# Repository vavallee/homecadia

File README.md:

<h1 align="center">
  <picture>
    <source media="(prefers-color-scheme: dark)" srcset="docs/img/logo-dark.svg">
    
  </picture>
</h1>

<!-- Logo: the Grand-Pré Memorial Church (Grand-Pré National Historic Site, Nova
     Scotia) behind the case wordmark; drawn without religious symbols. -->

**A battery-powered Matter-over-Thread room sensor for Home Assistant, built
from scratch on the ESP32-C6 with esp-matter and ESP-IDF. 125 µA average,
e-ink display, rotary dial, no cloud, no Wi-Fi, and every trap written down.**

<!-- photo replaces the render once a unit is assembled:  -->

A room temperature and humidity sensor that reports to Home Assistant over
Thread as a Matter sleepy end device, shows its own readings on a 2.9" e-ink
panel, and takes input from a rotary dial. It averages **125 µA** measured on
the bench, about eighteen months on one 2000 mAh cell at 85 % usable. No vendor
cloud, no hub beyond a Thread border router, and no Wi-Fi: the radio is
compiled out.

Everything is here: firmware, drivers, pin map with schematic-verified board
facts, measured power budget, 3D-printable enclosure, bill of materials with
real prices, and the reasoning behind each decision, including the ones that
turned out wrong.

## At a glance

| | |
|---|---|
| MCU | Seeed XIAO ESP32-C6 (RISC-V, 802.15.4 + BLE; Wi-Fi compiled out) |
| Firmware | **aardvark** (Matter model name and version string, e.g. `aardvark 0.7.0`; build output `aardvark.bin`, OTA image `aardvark-<version>.ota`) |
| Stack | [esp-matter](https://github.com/espressif/esp-matter) v1.6 on ESP-IDF v5.5.5, C++ |
| Network | Matter over Thread, OpenThread minimal device (MTD), commissioned over BLE |
| Power mode | Intermittently Connected Device (ICD), short idle time: 15 s parent polls, 600 s idle interval, automatic light sleep |
| Controller | Home Assistant with matterjs-server, Home Assistant Connect ZBT-2 border router |
| Clusters | Temperature Measurement, Relative Humidity Measurement, Power Source (battery % and voltage), Thread Network Diagnostics with counters |
| Measured current | **125 µA** paired and settled (sleep floor 57 µA, parent poll ~0.48 mC); **19.7 µA** unpaired in deep sleep |
| Display | 2.9" 296×128 SSD1680 e-paper, partial refresh ~6–7.5 mC, full ~19 mC |
| Status | One unit bench-verified on a Nordic PPK2; enclosure being redesigned |

## If you are building Matter or Thread devices on an ESP32

Most of this repo is reusable even if you never build this sensor. The
findings that took longest, with where to read them:

| Topic | Where |
|---|---|
| Getting an ESP32-C6 Matter device from ~376 µA to 125 µA: ADC power domain, bus power-down flags, ICD mode, a pin regression | [power-budget.md](docs/power-budget.md), [field-notes](docs/field-notes.md) §20–§22, §28 |
| Long Idle Time ICD buys nothing with Home Assistant (no check-in client) and costs ~67 µA; what to use instead | [retro](docs/retro.md) M8, [sdkconfig.defaults](firmware/sensor-01/sdkconfig.defaults) |
| A non-wake GPIO with a level interrupt under `CONFIG_PM_SLP_DISABLE_GPIO`: +16 µA floor, polls 60 % dearer | [field-notes](docs/field-notes.md) §28 |
| Waking light sleep from a rotary encoder: LP GPIOs only, level not edge | [field-notes](docs/field-notes.md) §21, [`ec11_encoder`](firmware/components/ec11_encoder) |
| An unpaired Matter device draws 28 mA; deep sleep that works (restart, then sleep before the stack starts) | [field-notes](docs/field-notes.md) §26–§27 |
| `attribute::update()` silently does nothing for code-driven clusters in esp-matter v1.6 | [field-notes](docs/field-notes.md) §9 |
| Commissioning to Home Assistant without HAOS: test certificates, BLE proxy, border router | [commissioning.md](docs/commissioning.md) |
| Thread coverage, border-router outages, a bare XIAO ESP32-C6 as a Thread router | [field-notes](docs/field-notes.md) §6–§7, §24, [infrastructure.md](docs/infrastructure.md), [bringup.md](docs/bringup.md) Radio / Matter |
| Measuring µA on a sleepy radio device with a PPK2, and analysing captures offline | [`tools/ppk2-events.py`](tools/ppk2-events.py), [retro](docs/retro.md) T7–T9 |
| Hardware bring-up traps: FPC ribbons, flux, underside pads, breadboard battery paths | [assembly.md](docs/assembly.md), [battery-runbook.md](docs/battery-runbook.md), [field-notes](docs/field-notes.md) §15–§19, §25 |
| Eight weeks of bring-up in one place: what went wrong, why, and the checklist for the next unit | [retro.md](docs/retro.md) |

> **Status: bench-verified, not yet assembled.** One unit runs on the bench
> (XIAO, driver board, panel, SHT40, encoder on a breadboard) with a Nordic
> PPK2 standing in for the cell. Verified there: commissioning to Home
> Assistant over Thread, display output, battery-voltage reading (within 3 mV
> of a meter, 3.4–4.0 V), **125 µA settled paired current** (2026-10-05),
> 19.7 µA unpaired deep sleep, and the dial waking the chip from light sleep on
> battery power. It has run 21 h on a real LiPo with no restart. **Not yet
> done:** a long soak on a real cell, and the enclosure, which is being
> redesigned. Open rows are in [docs/bringup.md](docs/bringup.md); code written
> ahead of hardware is marked `HW-VERIFY` and tracked there. The build
> procedure, with a test gate after every soldering stage, is
> [docs/assembly.md](docs/assembly.md).

## Devices

| Device | Status | Description |
|---|---|---|
| [sensor-01](firmware/sensor-01/) | in development | Battery-powered room temp/humidity sensor. 2.9" e-ink display, rotary dial, Matter-over-Thread sleepy end device (SIT ICD). 3 units. |

## What you can lift from here

The drivers are self-contained ESP-IDF components with no dependencies beyond
the IDF itself. Copy the directory into your own `components/` and it builds.
MIT licensed.

| Component | Why it might be useful |
|---|---|
| [`sht40`](firmware/components/sht40) | Sensirion SHT40 on the ESP-IDF 5.x `i2c_master` API (not the deprecated legacy driver), high-precision single-shot with CRC-8 validation |
| [`ssd1680`](firmware/components/ssd1680) | 2.9" e-paper with **differential partial refresh**, periodic full refresh to clear ghosting, and panel deep sleep between updates — the parts most sample code leaves out |
| [`monogfx`](firmware/components/monogfx) | 1-bit framebuffer renderer with a scaled 5×7 font and a seven-segment digit routine. No LVGL, no external graphics library |
| [`ec11_encoder`](firmware/components/ec11_encoder) | EC11 rotary encoder decoded from a Gray-code transition table in an ISR — bounce-immune without debounce delays, and draws no idle current |

Tools, usable on any project:

| Tool | What it does |
|---|---|
| [`tools/ppk2-events.py`](tools/ppk2-events.py) | Reads a Nordic PPK2 `.ppk2` capture offline and splits it into sleep floor, radio polls, bursts and short wakes with their charge, so one capture gives a per-item current budget |
| [`tools/matter-node.py`](tools/matter-node.py) | Reads a node through the Home Assistant Matter server WebSocket: the cached attributes (free for the device) or a forced interview |
| [`tools/check-profiles.sh`](tools/check-profiles.sh) | Asserts a shipping and a bench sdkconfig really differ on sleep, and that test-only options are off in shipping. Runs in CI |

Also reusable regardless of hardware: the
[power budget](docs/power-budget.md) and the firmware policies it forced, the
[retro](docs/retro.md), and the [documented traps](#traps-that-cost-time)
below.

## Features

Firmware capabilities, all implemented in this repo unless noted:

- **Matter over Thread**, Wi-Fi compiled out. OpenThread MTD, commissioned over
  Bluetooth Low Energy, joins via any OpenThread border router (developed
  against Home Assistant Connect ZBT-2).
- **Short Idle Time ICD** (Intermittently Connected Device): automatic light
  sleep between 15 s parent polls, and a 600 s idle interval that the device
  offers as its subscription max interval, so a report with nothing new goes
  out every 10 min. Long Idle Time was dropped on 2026-10-04: Home Assistant
  registers no check-in client, so it only added cost
  ([retro](docs/retro.md) M8).
- **Unpaired deep sleep**: a unit nobody pairs deep-sleeps at 19.7 µA once
  its 15-minute commissioning window closes, and a turn of the dial starts a
  new window ([field-notes](docs/field-notes.md) §27).
- **Thread Network Diagnostics with counters** (attach attempts, parent
  changes, MAC retries), readable from the controller at no reporting cost.
- **Matter clusters**: TemperatureMeasurement, RelativeHumidityMeasurement, and
  PowerSource with battery percentage and voltage.
- **Delta-gated reporting** — a report is sent on ≥0.2 °C / ≥1 %RH change, with
  a forced heartbeat every N polls, instead of on every sample.
- **SHT40 driver** (`firmware/components/sht40`) on the ESP-IDF 5.x
  `i2c_master` API, high-precision single-shot with Sensirion CRC-8 checking.
- **SSD1680 e-paper driver** (`firmware/components/ssd1680`) with differential
  partial refresh, periodic full refresh for ghosting, and panel deep sleep
  between updates.
- **1-bit framebuffer renderer** (`firmware/components/monogfx`) with a scaled
  5×7 font and a seven-segment digit routine — no external graphics library.
- **EC11 rotary encoder** (`firmware/components/ec11_encoder`) decoded from a
  Gray-code transition table in an interrupt handler: bounce-immune and drawing
  no idle current.
- **Local-only UI**: readings, diagnostics, and settings views; settings persist
  in NVS. The display never renders Home Assistant state — it shows what this
  device measured.
- **Battery monitoring** via a 2×1 MΩ + 100 nF divider on GPIO4 (an underside
  pad): 64 one-shot ADC samples after a 20 ms settle, eFuse curve-fitting
  calibration, and a scale factor fitted against a metered source to correct the
  ADC input loading the 500 kΩ divider. Open-circuit-voltage lookup table for
  percent.
- **Dial wakes the chip** from light sleep on a detent (encoder A on an LP
  GPIO underside pad, level-triggered).
- **Factory reset** on a 10-second encoder press (turn first: the switch is on
  a pin that cannot wake the chip); commissioning and low-battery states shown
  on a single LED and on the display.
- **CI** builds the flashable images on every push touching `firmware/**` and
  uploads them as an artifact.

## sensor-01 hardware

Seeed XIAO ESP32-C6 + Seeed ePaper Driver Board for XIAO V2 + 2.9" mono e-ink
(296×128, SSD1680) + Grove SHT40 + EC11 rotary encoder + 2000mAh LiPo, in a
wall-mount enclosure remixed from [veltoc](https://github.com/danking6/veltoc)
([hardware/case](hardware/case/README.md) — rev 4, FDM PLA, laser-engraved
wordmark).

*Assembled view rendered from the enclosure STLs. Colours and finish are
indicative; no unit has been built yet.*

Full bill of materials: [docs/bom.md](docs/bom.md). Pin map with the
schematic-verified board facts behind this diagram:
[docs/pinmap.md](docs/pinmap.md). The official bare-board pinout is on the
[Seeed XIAO ESP32-C6 wiki](https://wiki.seeedstudio.com/xiao_esp32c6_getting_started/)
(not reproduced here — Seeed's wiki content is GPL-3.0, this repo is MIT).

⚠️ This build involves a bare lithium-polymer cell soldered directly to the
board. Read the polarity warning at the top of
[docs/assembly.md](docs/assembly.md) before connecting anything — reversed
polarity destroys the charge circuit, and damaged LiPo cells are a fire hazard.

## Firmware

Espressif [esp-matter](https://github.com/espressif/esp-matter) v1.6 on
ESP-IDF v5.5.5, C++. Thread only (Wi-Fi disabled), commissions over Bluetooth
Low Energy to Home Assistant via an OpenThread border router (Home Assistant
Connect ZBT-2). Build instructions: [docs/build.md](docs/build.md).

The device advertises Espressif's **test vendor ID 0xFFF1** and shared test
commissioning credentials. It is not a Matter-certified product; controllers
will show an uncertified-device warning. Per-device factory partitions
(`esp-matter-mfg-tool`) are an open work item — see
[docs/commissioning.md](docs/commissioning.md).

## Documentation

| Doc | Contents |
|---|---|
| [docs/bom.md](docs/bom.md) | Bill of materials, part SKUs, divider-value rationale |
| [docs/pinmap.md](docs/pinmap.md) | Pin assignments and schematic-verified XIAO ESP32-C6 board facts |
| [docs/assembly.md](docs/assembly.md) | Wiring and build order, battery-polarity warning |
| [docs/build.md](docs/build.md) | Pinned toolchain SHAs, Docker and native builds, flashing from WSL2 |
| [docs/commissioning.md](docs/commissioning.md) | Pairing to Home Assistant: the three preconditions, the BLE-proxy workaround, factory reset. Apple Home is not available here and the doc says why |
| [docs/retro.md](docs/retro.md) | **Retrospective of the whole bring-up**: lessons, timeline, every problem with its cause and rule, the checklist for the next unit, open questions |
| [docs/field-notes.md](docs/field-notes.md) | **Traps that cost real time during bring-up**, one numbered section per incident (cited as §n). Read before bringing up another unit |
| [docs/power-budget.md](docs/power-budget.md) | Modelled and measured current draw per item, battery-life calculator, the policies it forced |
| [docs/battery-runbook.md](docs/battery-runbook.md) | Why a pack reads 0 V or a unit resets on battery: protection-board causes, look-alikes, and the test order |
| [docs/bringup.md](docs/bringup.md) | Hardware verification checklist — every `HW-VERIFY` marker has a row |
| [docs/diagrams/](docs/diagrams/) | Bench wiring, battery/divider schematic, enclosure internals and the no-solder bring-up ladder (self-contained HTML) |
| [docs/infrastructure.md](docs/infrastructure.md) | Network-side hardware: ZBT-2 border router, Thread coverage, Voice PE, order status |
| [docs/source-reliability.md](docs/source-reliability.md) | Documented traps in vendor docs and third-party sources |
| [hardware/case/README.md](hardware/case/README.md) | Enclosure: revision history, measured wall thicknesses, print vendor and material, engraving artwork |
| [circuit-board-maker/](circuit-board-maker/README.md) | Custom-PCB evaluation and two paper board designs. **Concluded: not worth it for three units.** Never fabricated — see the conflicts list before reviving it |

## Traps that cost time

Findings that aren't in any datasheet, written down so the next person doesn't
pay for them twice. Full list in
[docs/source-reliability.md](docs/source-reliability.md) and
[docs/pinmap.md](docs/pinmap.md).

- **A0 and D0 are the same pin on the XIAO ESP32-C6.** If your display uses D0
  for reset, the obvious ADC pin is gone. Battery sense moved to an underside
  test pad ([pinmap](docs/pinmap.md)).
- **The C6's RF switch is off at reset.** GPIO3 has a 10k pull-up and must be
  driven low in firmware before the antenna works; GPIO14 selects onboard
  ceramic versus U.FL. Neither pin is on the header. Schematic-verified.
- **espboards.dev pin tables are wrong for the C6** — they're shared boilerplate
  across ESP32 variants.
- **The Seeed wiki's battery-sense snippet doesn't apply.** It assumes an
  onboard divider the C6 schematic shows isn't populated.
- **A 100k battery divider costs ~9% of a 300µA budget.** 2×1MΩ + 100nF instead,
  at the price of a high-impedance ADC source ([power budget](docs/power-budget.md)).
- **A live ADC unit keeps the C6's radio power domain on through every light
  sleep** (~95 µA). Create and delete the unit per reading, and hold a
  no-light-sleep lock across it or the chip can fail to wake
  ([field notes](docs/field-notes.md) §21).
- **The chip only powers down its peripherals in light sleep if every I2C and
  SPI bus asks for it** (`flags.allow_pd`, `SPICOMMON_BUSFLAG_SLP_ALLOW_PD`).
  Without them the sleep floor was 279 µA; with them, 56 µA (§21).
- **A multimeter on a high-impedance node is a load, not a reference.** A 10 MΩ
  meter reads a 1 MΩ:1 MΩ divider midpoint ~5 % low. Calibrate the ADC against
  the supply, end to end (§23).
- **Light sleep kills the USB serial port in ~2 seconds**, which makes a board
  effectively unflashable without `CONFIG_USJ_NO_AUTO_LS_ON_CONNECTION`
  ([build](docs/build.md) has the recovery procedure, including the WSL2/usbipd
  quirks).
- **Opening `/dev/ttyACM0` with a plain shell read can hard-reset the chip** —
  it pulses the USB-Serial-JTAG control lines. Use `idf.py monitor`.
- **Seeed's sleep-current figures are for a bare board.** Measured on this build:
  a 45–57 µA light-sleep floor once the fixes here were in; 376 µA before
  them ([power budget](docs/power-budget.md)).
- **Long Idle Time ICD does nothing for you under Home Assistant.** No
  check-in client registers, so the device runs short-idle mode anyway, while
  LIT forces a 5 s minimum active period after every exchange and an extra
  wake a minute. Turning it off and raising the idle interval to 600 s took
  the average from 307 to 185 µA ([retro](docs/retro.md) M8).
- **A non-wake GPIO with a level interrupt reads as triggered in light sleep.**
  With `CONFIG_PM_SLP_DISABLE_GPIO`, pins that are not wake sources are
  isolated and read low. A push switch on an HP pin with a low-level interrupt
  raised the floor 16 µA and made every Thread poll 60 % dearer;
  `gpio_sleep_sel_dis()` fixed it, 185 → 125 µA (§28).
- **Only LP GPIOs (0–7) wake the C6 from light sleep with peripheral
  power-down on, and only on a level.** On the XIAO the free LP pins are
  underside pads (§21, [pinmap](docs/pinmap.md)).
- **An unpaired Matter device on the C6 never light-sleeps and draws ~28 mA.**
  `esp_deep_sleep_start()` from the running stack hung or stuck at 20 mA; what
  worked is restarting and entering deep sleep at the top of the next boot,
  before Bluetooth, Thread or power management start (§26–§27).
- **A USB host keeps the C6 out of light sleep**, so a sleep bug can be
  invisible for weeks on the bench. Test sleep on battery or a PPK2 with USB
  out (§20).
- **A breadboard row in the battery path brown-outs the radio.** Thousands of
  restarts read as a firmware fault; the Matter `bootReason` attribute said
  brown-out all along ([battery-runbook](docs/battery-runbook.md) B3).

## Milestones

| # | Deliverable | Status |
|---|---|---|
| 1 | Repo scaffold, docs, CI compiling an esp-matter skeleton for esp32c6 | done |
| 2 | Matter temp/humidity over Thread, commissions to HA (TinyENV parity) | **done 2026-08-23** — commissioned to HA over ZBT-2 OTBR, readings live in HA; see `docs/field-notes.md` for the preconditions |
| 3 | Display driver, view 1 rendering readings, measured refresh cost | **done** — display verified 2026-08-22 (full 1.79 s / partial 0.54 s BUSY); refresh charge measured 2026-10-05: partial ~6–7.5 mC, full ~19 mC |
| 4 | Encoder, views, settings, wake behavior | **done 2026-09-28** — a detent wakes the chip from light sleep on battery (encoder A on the MTCK pad); the push switch registers within 2 s of a turn |
| 5 | ICD tuning, battery reporting, power budget with measured numbers | **done** — 238 µA over 12.6 h (2026-09-22); **125 µA settled** after the ICD and pin fixes (2026-10-05); unpaired deep sleep 19.7 µA; battery voltage within 3 mV. See `docs/power-budget.md` |
| 6 | Factory reset, low-battery behavior, assembly guide final, v1.0.0 | factory reset + LED + low-bat display done; rest awaits hardware |

## Repo layout

```
docs/               BOM, pin map, assembly, commissioning, power budget, build,
                    field notes, retro
hardware/case/      wall-mount enclosure (veltoc remix, MIT) + engraving artwork
circuit-board-maker/ custom-PCB evaluation + two unfabricated KiCad designs
firmware/
  components/       drivers shared across future homecadia devices
  sensor-01/        esp-matter application
tools/              PPK2 capture analysis, Matter server node reader, profile check
.github/workflows/  CI: firmware build on push, .bin artifacts
```

## Building it yourself

1. **Read [docs/bom.md](docs/bom.md)** — real parts, real prices in CAD, real
   vendors, and which ones have known counterfeits or reversed polarity.
2. **Print the enclosure** from [hardware/case](hardware/case/README.md), or
   adapt it. The revision history there explains why each dimension is what it
   is, which matters if you swap the battery or the display.
3. **Build the firmware** with [docs/build.md](docs/build.md) — Docker path
   matches CI exactly and is the low-friction option.
4. **Wire it** using [docs/pinmap.md](docs/pinmap.md) and
   [docs/assembly.md](docs/assembly.md). Read the LiPo polarity warning first.
5. **Commission it** with [docs/commissioning.md](docs/commissioning.md), then
   work through [docs/bringup.md](docs/bringup.md).

Forking for different hardware? `firmware/sensor-01/main/app_config.h` is the
single source of pin truth and the place to start.

## Contributing

This is a personal build against one specific parts list, so the parts list, the
pinned toolchain and the locked design decisions are unlikely to change. That
said: **corrections are very welcome**, especially if you've measured something
this repo only models, or if one of the [traps](#traps-that-cost-time) turns out
to be wrong on your hardware. Issues and pull requests both fine.

If you are working on Matter or Thread devices on the ESP32-C6 (or H2, or any
ESP32 with an 802.15.4 radio) and hit something documented here, or something
that should be, open an issue: comparing measured numbers across boards is
the fastest way to tell a board quirk from a firmware one.

## License

MIT, see [LICENSE](LICENSE). Third-party attribution — including the veltoc
enclosure remix and the TinyENV architecture references — is in
[NOTICE.md](NOTICE.md).

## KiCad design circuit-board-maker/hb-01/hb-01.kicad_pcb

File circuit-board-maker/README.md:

# circuit-board-maker

Investigation into replacing the hand-wired sensor-01 build with a custom PCB,
and the board designs that came out of it.

> **Status: paper design, validated against KiCad 10.0.5 but never fabricated.**
> See [Validation](#validation) for exactly what was checked and what was not.

## Conclusion

**Don't build a full custom PCB for three units.** Build `hb-01`, hand-wire the
three units, and measure the assembled device before letting any power argument
justify a board spin. Full reasoning in [pcb-evaluation.md](pcb-evaluation.md).

## Conflicts with the shipped build — read before reviving hb-01

Audited 2026-08-13 against the main docs. None of these are fatal to the
evaluation's conclusion, but every one must be resolved before `hb-01` is
ordered.

1. **Two nets land on pins the XIAO header does not have.** `hb-01/NETLIST.md:54`
   routes `VDIV` to J2.13 and `:44` routes `ENC_SW` to J2.14 on a 14-pin "XIAO
   field". Per [../docs/pinmap.md](../docs/pinmap.md), the battery divider is on
   **GPIO5/MTDI** and the encoder push on **GPIO6/MTCK** — both **underside
   pads**, not header pins. Either those two positions are meant as
   flying-wire landings (undocumented), or the design assumes access that does
   not exist. Until it is resolved, `pcb-evaluation.md:179` ("Zero firmware
   changes") is unproven.
2. **Board-mount USB-C contradicts the case and the bought part.**
   `hb-01/NETLIST.md:10` places a receptacle needing a rectangular cutout;
   case rev 4 has a **Ø12.8mm round hole** and the Gebildet 2-wire pigtail that
   fits it is **already delivered** ([../docs/bom.md](../docs/bom.md)). No case
   revision exists for this. `component-selection.md:133` concedes the point.
3. **It does not fit the cavity as designed.** The 48 × 40mm board has to live
   in a 106.64 × 47.9mm cavity that already holds a 48.5mm tray plus a 56mm
   cell — **2.1mm of slack**
   ([../hardware/case/README.md](../hardware/case/README.md)). Its four M2 holes
   on a 41 × 33mm pattern also cannot mount on the tray's four Ø2.4mm pegs on a
   17.0 × 21.0mm pattern, and the case has no other board mounts. Stack height
   inside 18.6mm is unbudgeted. `README.md` already admits the board "was never
   checked against the STLs".
4. **Board-mounting the LED and encoder fights the front panel.** `case-front.stl`
   carries the EC11 mount and the 3mm LED hole; `hb-01/NETLIST.md:18-19` puts
   both on the board at fixed coordinates, making board position mechanically
   load-bearing against a panel it was never fitted to.
   `component-selection.md:42` independently recommends keeping the LED on
   flying leads.
5. **sb-01 replaces a part already in hand.** The Grove SHT40 (SKU 101021032)
   shipped 3/3; `sb-01` substitutes a bare DFN-4 SHT40-AD1B needing reflow.
6. **Internal staleness.** Both netlists still say "Never opened in KiCad"
   (`hb-01/NETLIST.md:4`, `sb-01/NETLIST.md:4`), contradicting the validated
   status above. Satellite size is quoted as ~10 × 10mm in
   `pcb-evaluation.md:56` and `component-selection.md:49` but built at 14 × 16mm.

## Documents

| Doc | Contents |
|---|---|
| [pcb-evaluation.md](pcb-evaluation.md) | Three options costed, quiescent-current budgets, antenna clearance, firmware change surface, and why a PCB doesn't earn its cost at qty 3 |
| [component-selection.md](component-selection.md) | Board-mount part equivalents with live LCSC stock, and the three parts where board-mounting is a downgrade |

## Boards

| Board | Size | Purpose | Assembly | DRC |
|---|---|---|---|---|
| [hb-01/](hb-01/) | 48 × 40 mm | Harness board — divider, USB-C + CC resistors, ESD, encoder, LED, JSTs, 6 test points | **Hand-solderable** | 65 errors, all inside J1 — see below |
| [sb-01/](sb-01/) | 14 × 16 mm | SHT40 satellite, keeps the sensor out of MCU heat | Needs reflow or hot air | **0 errors** |

### hb-01

### sb-01

### How they connect

## Files per board

```
hb-01/
  hb-01.kicad_pro    project settings, net classes
  hb-01.kicad_pcb    board outline, mounting holes, silkscreen, 24 placed footprints with nets
  hb-01.net          KiCad netlist
  NETLIST.md         authoritative connection list + BOM with LCSC codes
```

There is no `.kicad_sch`. The netlist is the design; a schematic is a drawing of
it, and KiCad can generate one from the board. Open the `.kicad_pro`, and the
footprints are already placed with nets assigned — start by routing.

## Validation

Run against **KiCad 10.0.5** (Windows install, driven from WSL via
`kicad-cli.exe`). What that actually established:

**Verified:**

- **All 13 footprint library references resolve** against KiCad 10's installed
  libraries. One was wrong on the first pass and is fixed —
  `Sensirion_DFN-4-1EP_1.5x1.5mm_P0.8mm_EP0.7x0.9mm` does not exist; the real
  name is `Sensirion_DFN-4_1.5x1.5mm_P0.8mm_SHT4x_NoCentralPad`.
- **`kicad-cli pcb upgrade` accepted both boards** and rewrote them in the
  current format — KiCad parses them.
- **All 26 footprints place with nets assigned**, 0 missing.
- **J1's pads are byte-identical to the library footprint** after the
  generate-and-place round trip (17 pads compared, 0 differences).
- **Both boards render in 3D** — the images above are `kicad-cli pcb render`
  output, not drawings.
- **sb-01 passes DRC with 0 errors.**
- Encoder terminal geometry **checked against the Bourns PEC11R datasheet**:
  5 × Ø1.0 mm holes, 2.5 mm pitch, 5.0 mm spans — matches the footprint.

**Found and fixed during validation:**

- USB-C on hb-01 and the JST-SH on sb-01 both **hung off the board edge**.
- sb-01's C1 and J1 **collided** (courtyard overlap + clearance error).
- sb-01's silkscreen **overflowed a 12 × 16 mm board**; it is now 14 × 16 mm
  with a shorter silk string.
- D+/D− were documented as "broken out to test pads" but **were never actually
  netted**. They now go to TP5/TP6.

**Not resolved:**

- **hb-01 reports 65 DRC errors, every one of them inside J1** (the USB-C
  receptacle) and zero anywhere else. The XKB U262-16XN land pattern has 0.2 mm
  pad gaps, and `kicad-cli` runs with KiCad's default 0.2 mm clearance because
  this hand-written `.kicad_pro` is too minimal for it to load design rules
  from — setting the netclass to 0.05 mm changed nothing. **Open the project in
  the GUI once, set Board Setup → Constraints to 0.127 mm, and save.** That is
  the boundary where these generator scripts should stop and KiCad takes over.
- **Silkscreen sits over pads** on both boards (`silk_over_copper` warnings).
  On sb-01 this hides U1's 0.5 × 0.3 mm pads in the render — they are present
  and netted, just buried under the reference designator.
- **Nothing is routed.** hb-01 has 37 unconnected items, sb-01 has 6.
- **Board dimensions are not fitted to the case.** 48 × 40 mm was chosen to sit
  beside the LP103454 in the 106.64 × 47.9 mm cavity, but was never checked
  against the STLs in [hardware/case](../hardware/case/).
- **The Seeed driver board's IO breakout pinout is undocumented.** `J2` is a
  labelled 2.54 mm field, not a verified mating connector. Probe it when the
  board arrives.
- **The encoder's mounting-boss holes are unverified.** `PEC12R-3x17F-Sxxxx` is
  used because no PEC11R footprint ships with KiCad; its terminals match, but it
  drills 3.1 mm oval bosses and the PEC11R boss dimension could not be read
  reliably from the datasheet drawing. Check before ordering.
- **USB-C on hb-01 carries power only.** The XIAO does not expose D+/D− on its
  header, so flashing and console stay on the XIAO's own connector. TP5/TP6 are
  there for probing, not for a host connection.

## Regenerating

```
python3 gen.py      # netlists, .kicad_pcb outline, .kicad_pro, NETLIST.md
python3 place.py    # loads footprints from the KiCad libs and places them
python3 svg.py      # img/*.svg
```

`place.py` reads the KiCad footprint libraries from
`/mnt/c/Program Files/KiCad/10.0/share/kicad/footprints` — adjust that path
elsewhere. Edit the spec at the top of `gen.py` rather than the generated files.

Once the design moves into KiCad's GUI, **KiCad owns these files** and these
scripts should be retired — re-running them discards routing.

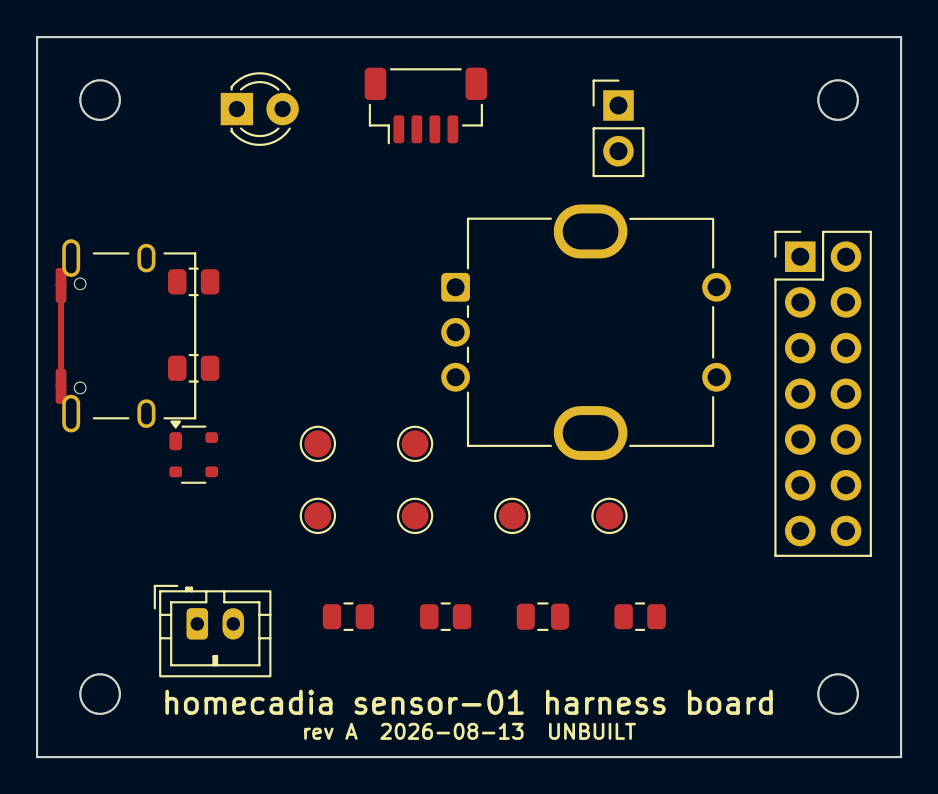
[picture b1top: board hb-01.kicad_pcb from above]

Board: 2 copper layers, 48.0 x 40.0 mm, 24 parts (0 on the bottom side), 16 nets, no tracks yet.

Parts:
C1: 100nF; C_0805_2012Metric
D1: SP0503BAHTG; SOT-143
D2: LED 3mm; LED_D3.0mm
H1, H2, H3, H4: M2; MountingHole_2.2mm_M2
J1: USB-C 16P; USB_C_Receptacle_XKB_U262-16XN-4BVC11
J2: XIAO field 2x7; PinHeader_2x07_P2.54mm_Vertical
J3: BAT JST-PH; JST_PH_B2B-PH-K_1x02_P2.00mm_Vertical
J4: SHT40 JST-SH; JST_SH_BM04B-SRSS-TB_1x04-1MP_P1.00mm_Vertical
J5: 5V out; PinHeader_1x02_P2.54mm_Vertical
R1, R2: 5.1k; R_0805_2012Metric
R3, R4: 1M 1%; R_0805_2012Metric
R5: 1k; R_0805_2012Metric
SW1: PEC11R-4220F-S0024; RotaryEncoder_Bourns_Vertical_PEC12R-3x17F-Sxxxx
TP1: VBAT; TestPoint_Pad_D1.5mm
TP2: VDIV; TestPoint_Pad_D1.5mm
TP3: GND; TestPoint_Pad_D1.5mm
TP4: 3V3; TestPoint_Pad_D1.5mm
TP5: USB_DP; TestPoint_Pad_D1.5mm
TP6: USB_DM; TestPoint_Pad_D1.5mm

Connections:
+3V3: J2.12, J4.1, TP4.1
CC1: J1.A5, R1.1
CC2: J1.B5, R2.1
ENC_A: J2.8, SW1.A
ENC_B: J2.10, SW1.B
ENC_SW: J2.14, SW1.S1
GND: C1.2, D1.2, D2.1, J1.A1, J1.A12, J1.B1, J1.B12, J2.1, J3.2, J4.4, J5.2, R1.2, R2.2, R4.2, SW1.C, SW1.S2, TP3.1
LED_A: J2.7, R5.1
LED_K: D2.2, R5.2
SCL: J2.6, J4.2
SDA: J2.5, J4.3
USB_DM: J1.A7, J1.B7, TP6.1
USB_DP: D1.1, J1.A6, J1.B6, TP5.1
VBAT: J3.1, R3.1, TP1.1
VBUS: D1.3, J1.A4, J1.A9, J1.B4, J1.B9, J5.1
VDIV: C1.1, J2.13, R3.2, R4.1, TP2.1

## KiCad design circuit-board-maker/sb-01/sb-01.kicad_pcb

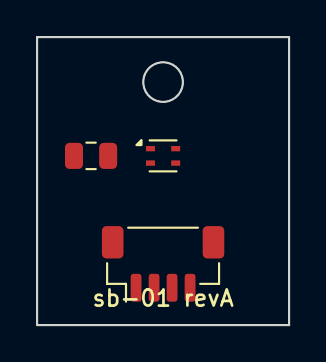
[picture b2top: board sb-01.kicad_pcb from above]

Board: 2 copper layers, 14.0 x 16.0 mm, 4 parts (0 on the bottom side), 4 nets, no tracks yet.

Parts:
C1: 100nF; C_0805_2012Metric
H1: M2; MountingHole_2.2mm_M2
J1: JST-SH 4P; JST_SH_BM04B-SRSS-TB_1x04-1MP_P1.00mm_Vertical
U1: SHT40-AD1B-R2; Sensirion_DFN-4_1.5x1.5mm_P0.8mm_SHT4x_NoCentralPad

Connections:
+3V3: C1.1, J1.1, U1.1
GND: C1.2, J1.4, U1.3
SCL: J1.2, U1.2
SDA: J1.3, U1.4
